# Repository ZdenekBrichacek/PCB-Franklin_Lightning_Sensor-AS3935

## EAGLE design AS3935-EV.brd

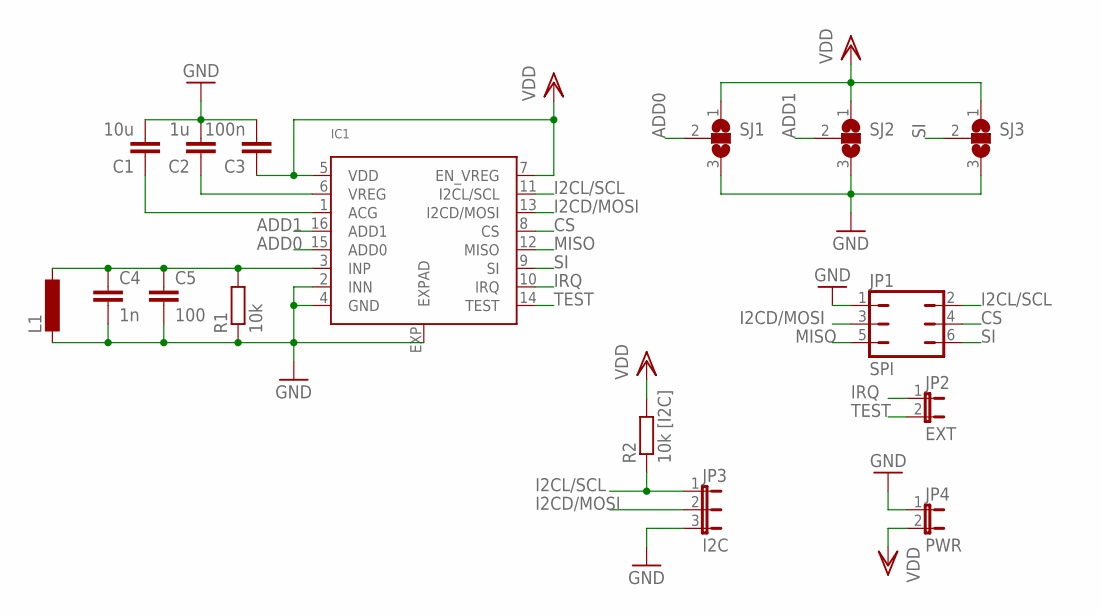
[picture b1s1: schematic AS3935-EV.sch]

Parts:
C1: 10u; C0805
C2: 1u; C0805
C3: 100n; C0603
C4: 1n; C0603
C5: 100; C0603
IC1: AS3935; 16LDMLPQ
JP1: SPI; JP3Q
JP2: EXT; JP1
JP3: I2C; JP2
JP4: PWR; JP1
L1: COILCRAFT
R1: 10k; R0603
R2: 10k [I2C]; R0603
SJ1, SJ2, SJ3: SJ2W; SJ_2

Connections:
ADD0: IC1.15 (ADD0), SJ1.2
ADD1: IC1.16 (ADD1), SJ2.2
CS: IC1.8 (CS), JP1.4
GND: C1.2, C2.2, C3.2, C4.2, C5.2, IC1.2 (INN), IC1.4 (GND), IC1.EXP (EXPAD), JP1.1, JP3.3, JP4.1, L1.2, R1.1, SJ1.3, SJ2.3, SJ3.3
I2CD/MOSI: IC1.13 (I2CD/MOSI), JP1.3, JP3.2
I2CL/SCL: IC1.11 (I2CL/SCL), JP1.2, JP3.1, R2.1
INP: C4.1, C5.1, IC1.3 (INP), L1.1, R1.2
IRQ: IC1.10 (IRQ), JP2.1
MISO: IC1.12 (MISO), JP1.5
unnamed: C2.1, IC1.6 (VREG)
unnamed: C1.1, IC1.1 (ACG)
SI: IC1.9 (SI), JP1.6, SJ3.2
TEST: IC1.14 (TEST), JP2.2
VDD: C3.1, IC1.5 (VDD), IC1.7 (EN_VREG), JP4.2, R2.2, SJ1.1, SJ2.1, SJ3.1

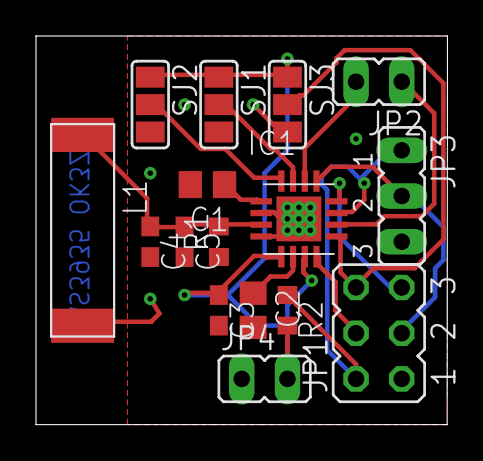
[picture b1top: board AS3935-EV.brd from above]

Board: 2 copper layers, 22.9 x 21.6 mm, 16 parts (0 on the bottom side), 14 nets.

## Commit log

2017-10-10 :circus_tent: Added .gitattributes & .gitignore files
2017-10-10 Initial version
